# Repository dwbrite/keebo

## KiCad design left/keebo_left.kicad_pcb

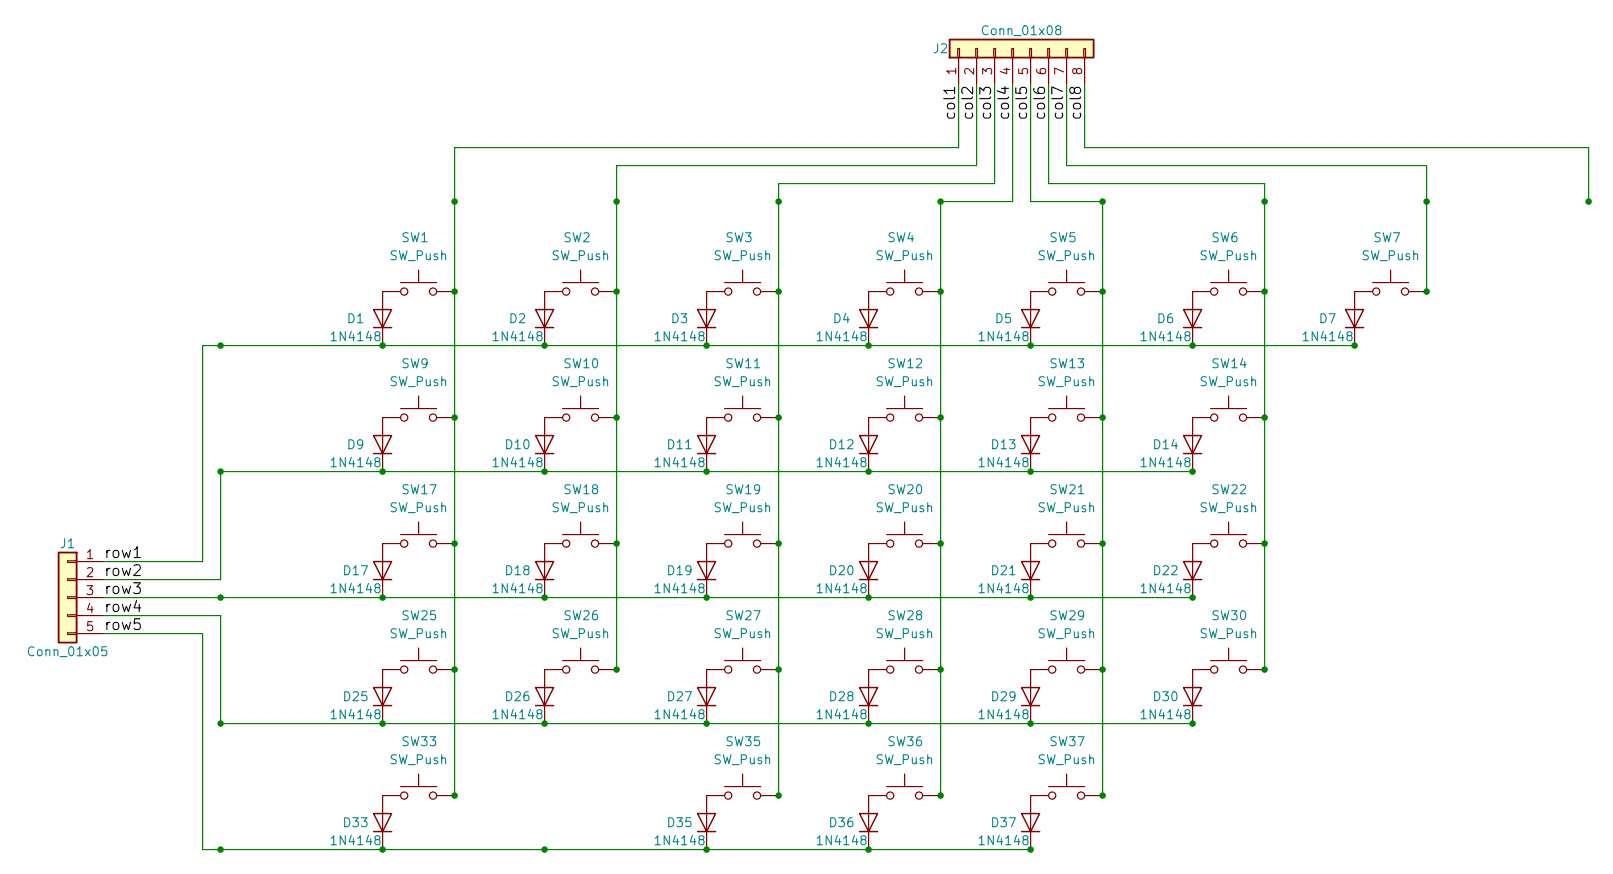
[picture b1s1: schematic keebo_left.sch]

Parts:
D1, D2, D3, D4, D5, D6, D7, D9, D10, D11, D12, D13, D14, D17, D18, D19, D20, D21, D22, D25, D26, D27, D28, D29, D30, D33, D35, D36, D37: 1N4148; D_DO-35_SOD27_P2.54mm_Vertical_AnodeUp
J1: Conn_01x05; 2mm_Pads_01x05
J2: Conn_01x08; 2mm_Pads_01x08
SW1, SW2, SW3, SW4, SW5, SW6, SW7, SW10, SW11, SW12, SW13, SW14, SW18, SW19, SW20, SW21, SW22, SW26, SW27, SW28, SW29, SW30: SW_Push; KeeboHR_100_MX
SW9: SW_Push; KeeboHR_150_MX
SW17: SW_Push; KeeboHR_175_MX
SW25: SW_Push; KeeboHR_225_MX
SW33, SW35, SW36, SW37: SW_Push; KeeboHR_125_MX

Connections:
/col1: J2.1, SW1.2, SW9.2, SW17.2, SW25.2, SW33.2
/col2: J2.2, SW2.2, SW10.2, SW18.2, SW26.2
/col3: J2.3, SW3.2, SW11.2, SW19.2, SW27.2, SW35.2
/col4: J2.4, SW4.2, SW12.2, SW20.2, SW28.2, SW36.2
/col5: J2.5, SW5.2, SW13.2, SW21.2, SW29.2, SW37.2
/col6: J2.6, SW6.2, SW14.2, SW22.2, SW30.2
/col7: J2.7, SW7.2
/row1: D1.1 (K), D2.1 (K), D3.1 (K), D4.1 (K), D5.1 (K), D6.1 (K), D7.1 (K), J1.1
/row2: D9.1 (K), D10.1 (K), D11.1 (K), D12.1 (K), D13.1 (K), D14.1 (K), J1.2
/row3: D17.1 (K), D18.1 (K), D19.1 (K), D20.1 (K), D21.1 (K), D22.1 (K), J1.3
/row4: D25.1 (K), D26.1 (K), D27.1 (K), D28.1 (K), D29.1 (K), D30.1 (K), J1.4
/row5: D33.1 (K), D35.1 (K), D36.1 (K), D37.1 (K), J1.5
unnamed: D1.2 (A), SW1.1
unnamed: D2.2 (A), SW2.1
unnamed: D3.2 (A), SW3.1
unnamed: D4.2 (A), SW4.1
unnamed: D5.2 (A), SW5.1
unnamed: D6.2 (A), SW6.1
unnamed: D7.2 (A), SW7.1
unnamed: D9.2 (A), SW9.1
unnamed: D10.2 (A), SW10.1
unnamed: D11.2 (A), SW11.1
unnamed: D12.2 (A), SW12.1
unnamed: D13.2 (A), SW13.1
unnamed: D14.2 (A), SW14.1
unnamed: D17.2 (A), SW17.1
unnamed: D18.2 (A), SW18.1
unnamed: D19.2 (A), SW19.1
unnamed: D20.2 (A), SW20.1
unnamed: D21.2 (A), SW21.1
unnamed: D22.2 (A), SW22.1
unnamed: D25.2 (A), SW25.1
unnamed: D26.2 (A), SW26.1
unnamed: D27.2 (A), SW27.1
unnamed: D28.2 (A), SW28.1
unnamed: D29.2 (A), SW29.1
unnamed: D30.2 (A), SW30.1
unnamed: D33.2 (A), SW33.1
unnamed: D35.2 (A), SW35.1
unnamed: D36.2 (A), SW36.1
unnamed: D37.2 (A), SW37.1

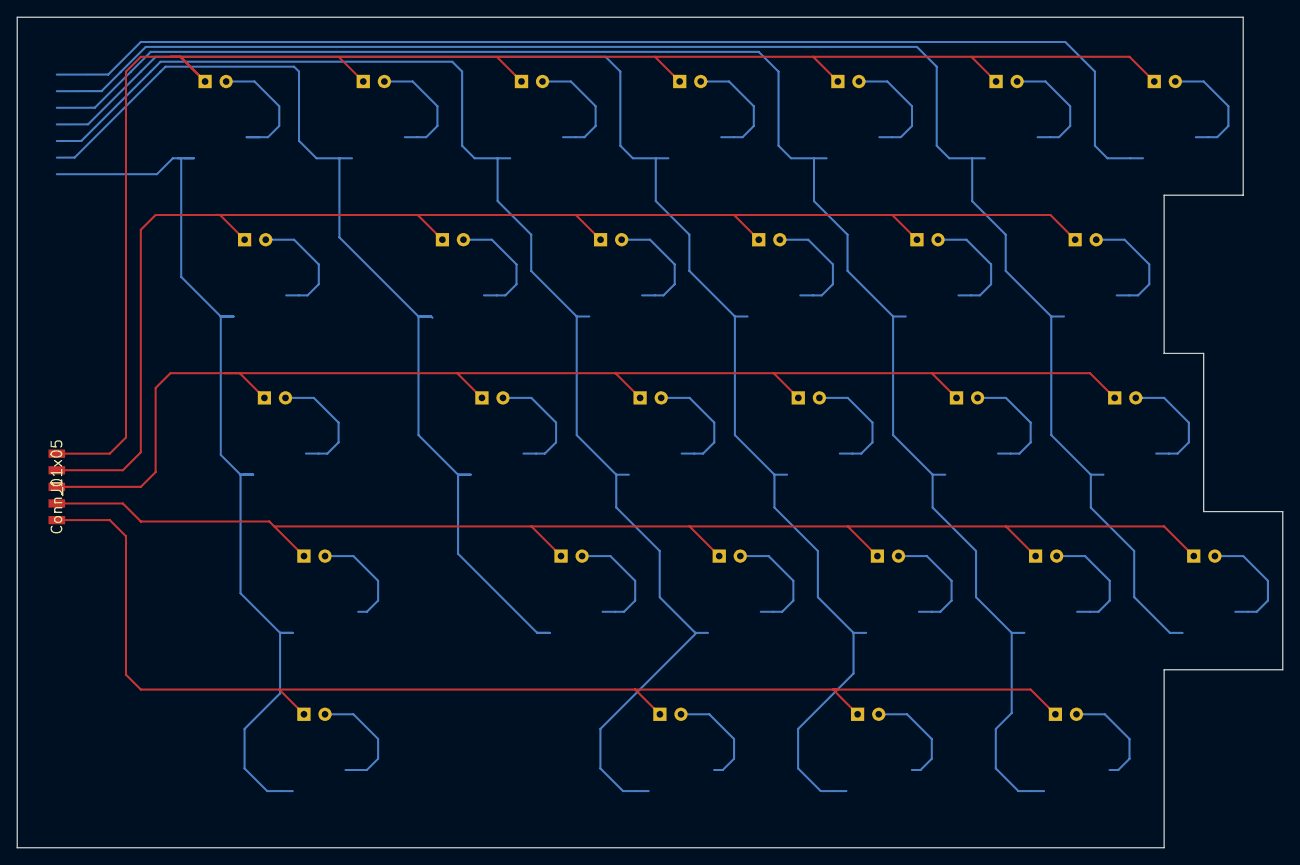
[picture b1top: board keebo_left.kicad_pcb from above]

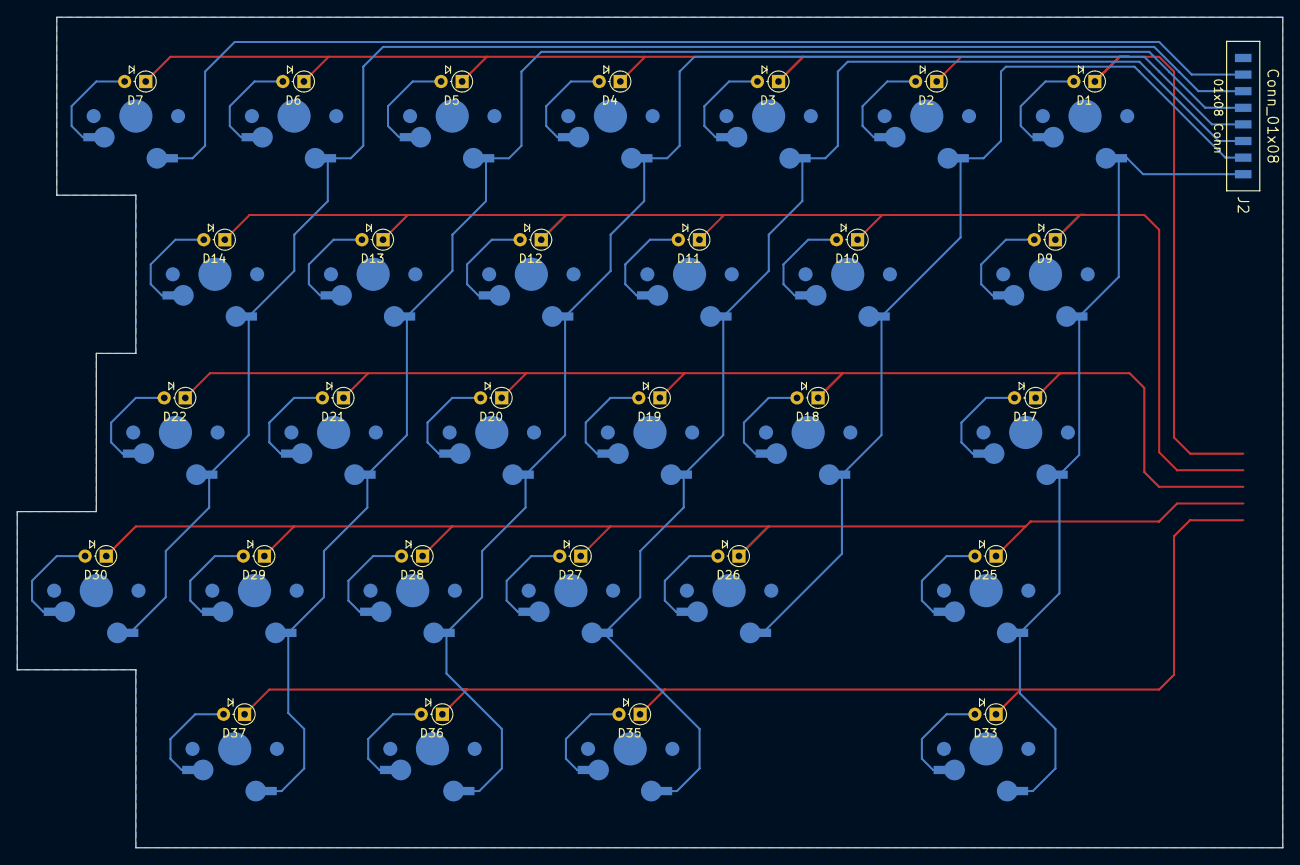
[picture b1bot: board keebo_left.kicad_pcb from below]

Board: 2 copper layers, 152.4 x 100.0 mm, 60 parts (59 on the bottom side), 41 nets.

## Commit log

2018-04-22 create inital pcb (wip)
2018-04-23 Make dependencies use relative path
2018-04-26 Remove separate components
2018-04-26 Create PCB for low profile switches
2018-05-16 Remove unnecessary files; move low-profile to a new branch
2018-05-16 Add missing *.bak pattern in .gitignore
2018-05-16 Begin recreating standard profile layout
2018-05-21 Add custom generated switch footprints (with source code)
2018-05-23 Create left board using new switch footprints
2018-06-28 Fix key matrix; use MX exclusively; Fix MX missing side holes.
